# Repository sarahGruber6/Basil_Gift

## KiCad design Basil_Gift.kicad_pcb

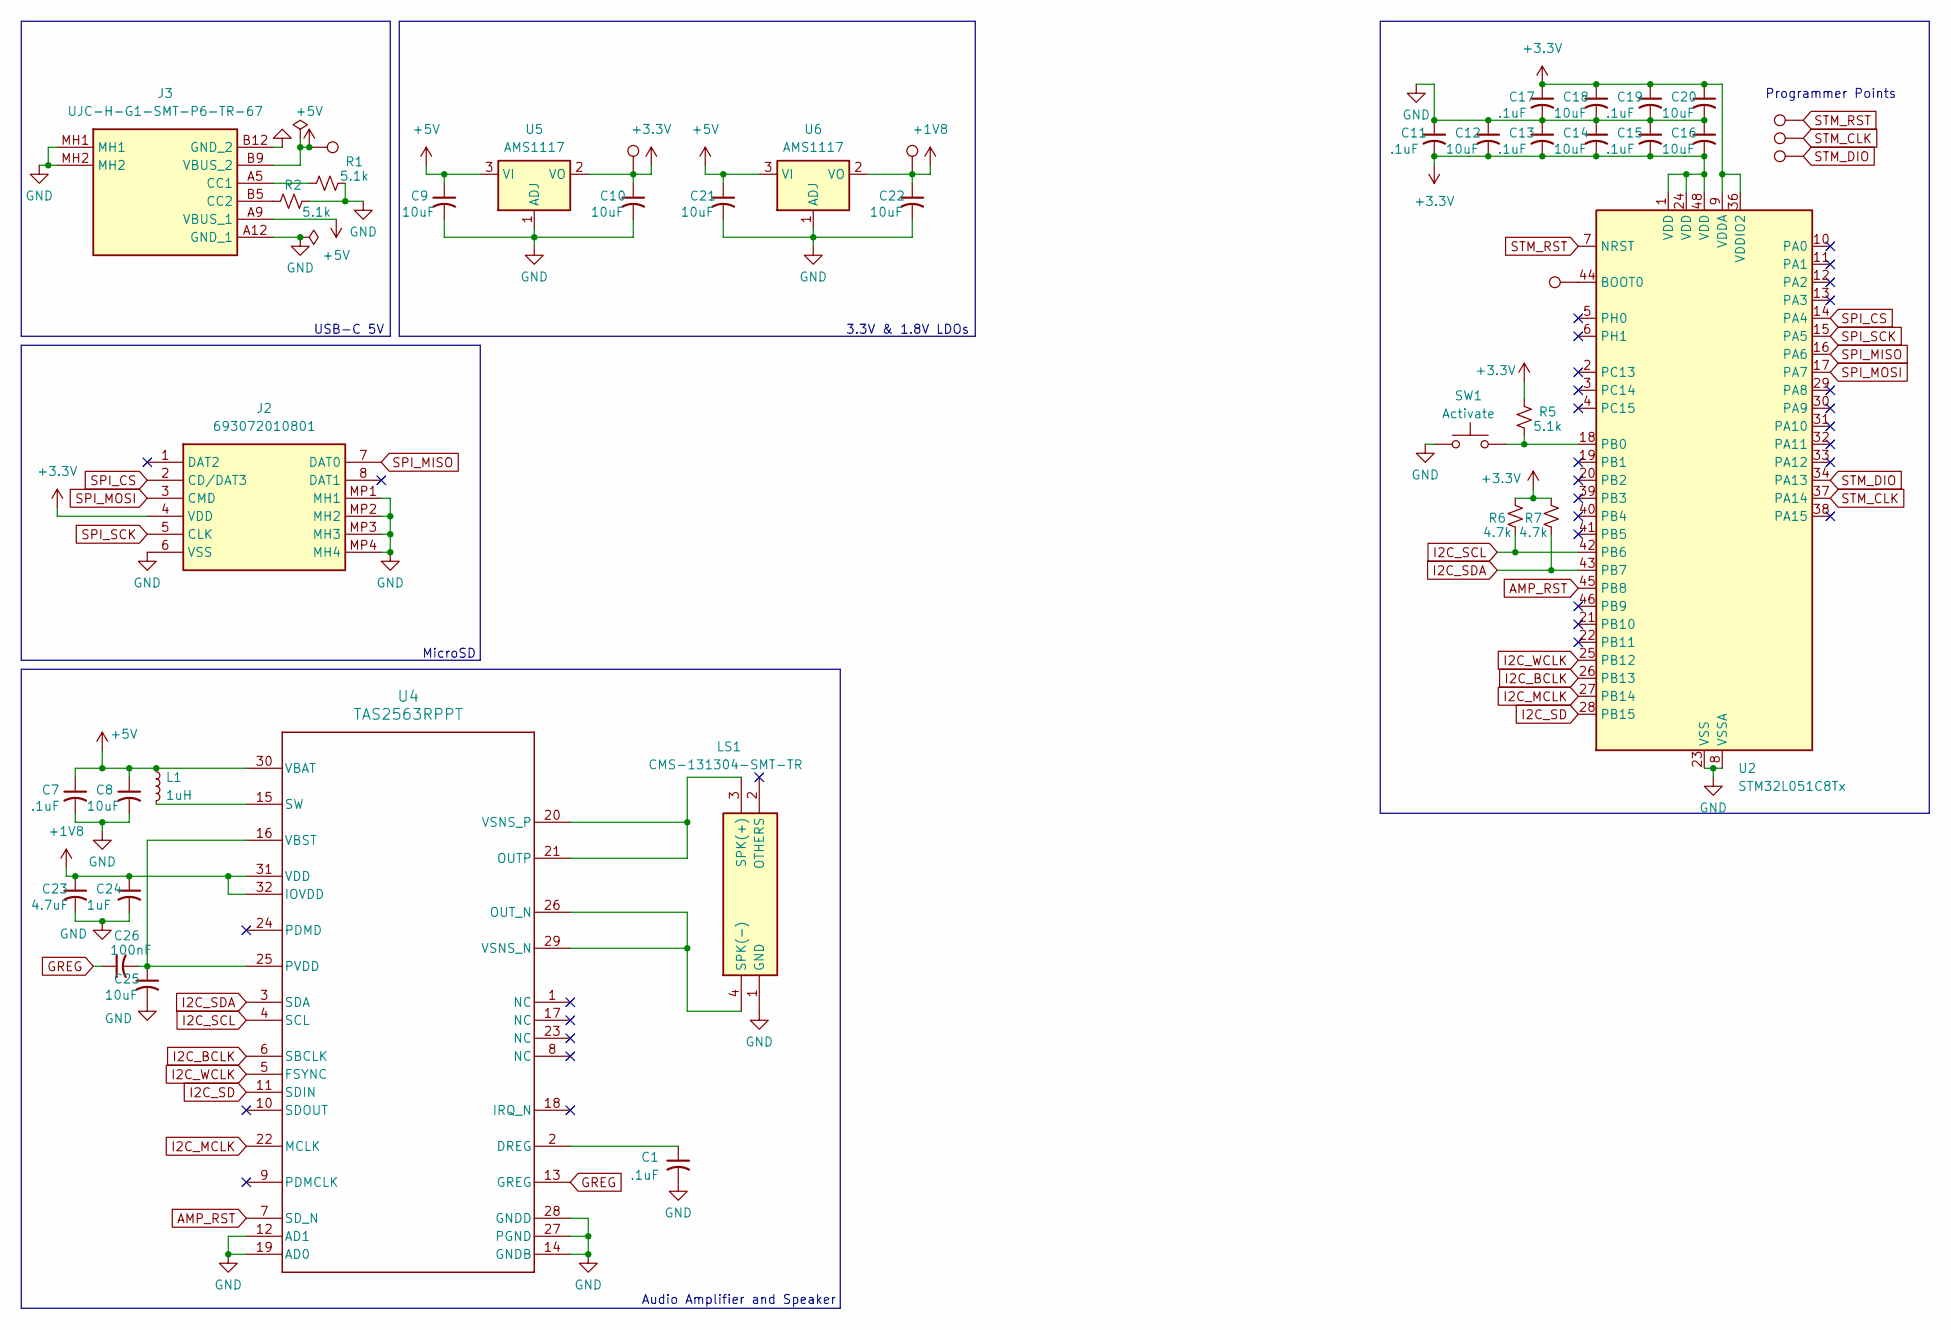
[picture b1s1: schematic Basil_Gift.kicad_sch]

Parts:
C1, C7, C11, C13, C15, C17, C19: .1uF; C_0603_1608Metric_Pad1.08x0.95mm_HandSolder
C8, C9, C10, C12, C14, C16, C18, C20, C21, C22, C25: 10uF; C_0603_1608Metric_Pad1.08x0.95mm_HandSolder
C23: 4.7uF; C_0603_1608Metric_Pad1.08x0.95mm_HandSolder
C24: 1uF; C_0603_1608Metric_Pad1.08x0.95mm_HandSolder
C26: 100nF; C_0603_1608Metric_Pad1.08x0.95mm_HandSolder
J2: 693072010801; Mouser Part Number 710-693072010801
J3: UJC-H-G1-SMT-P6-TR-67; UJCHG1SMTP6TR67; Manufacturer_Part_Number UJC-H-G1-SMT-P6-TR-67
L1: 1uH; L_0603_1608Metric_Pad1.05x0.95mm_HandSolder
LS1: CMS-131304-SMT-TR; CMS131304SMTTR; PARTREV 1.02; Mouser Part Number 179-CMS-131304-SMTTR
R1, R2, R5: 5.1k; R_0603_1608Metric_Pad0.98x0.95mm_HandSolder
R6, R7: 4.7k; R_0603_1608Metric_Pad0.98x0.95mm_HandSolder
SW1: Activate; SW_SPST_EVQP0
TP1, TP2, TP4, TP7, TP8, TP9, TP10: TestPoint; TestPoint_Pad_D1.5mm
U2: STM32L051C8Tx; LQFP-48_7x7mm_P0.5mm
U4: TAS2563RPPT; RPP0032B-MFG
U5, U6: AMS1117; SOT-223-3_TabPin2

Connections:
+1V8: C22.1, C23.1, C24.1, TP10.1 (1_1), U4.31 (VDD), U4.32 (IOVDD), U6.2 (VO)
+3.3V: C10.1, C11.2, C12.2, C13.2, C14.2, C15.2, C16.2, C17.1, C18.1, C19.1, C20.1, J2.4 (VDD), R5.2, R6.2, R7.2, TP4.1 (1_1), U2.1 (VDD), U2.9 (VDDA), U2.24 (VDD), U2.36 (VDDIO2), U2.48 (VDD), U5.2 (VO)
+5V: C7.1, C8.1, C9.1, C21.1, J3.A9 (VBUS_1), J3.B9 (VBUS_2), L1.1, TP2.1 (1_1), U4.30 (VBAT), U5.3 (VI), U6.3 (VI)
AMP_RST: U2.45 (PB8), U4.7 (SD_N)
GND: C1.2, C7.2, C8.2, C9.2, C10.2, C11.1, C12.1, C13.1, C14.1, C15.1, C16.1, C17.2, C18.2, C19.2, C20.2, C21.2, C22.2, C23.2, C24.2, C25.2, J2.6 (VSS), J2.MP1 (MH1), J2.MP2 (MH2), J2.MP3 (MH3), J2.MP4 (MH4), J3.A12 (GND_1), J3.B12 (GND_2), J3.MH1, J3.MH2, LS1.1 (GND), R1.2, R2.2, SW1.1, U2.8 (VSSA), U2.23 (VSS), U2.35 (VSS), U2.47 (VSS), U4.12 (AD1), U4.14 (GNDB), U4.19 (AD0), U4.27 (PGND), U4.28 (GNDD), U5.1 (ADJ), U6.1 (ADJ)
GREG: C26.1, U4.13 (GREG)
I2C_BCLK: U2.26 (PB13), U4.6 (SBCLK)
I2C_MCLK: U2.27 (PB14), U4.22 (MCLK)
I2C_SCL: R6.1, U2.42 (PB6), U4.4 (SCL)
I2C_SD: U2.28 (PB15), U4.11 (SDIN)
I2C_SDA: R7.1, U2.43 (PB7), U4.3 (SDA)
I2C_WCLK: U2.25 (PB12), U4.5 (FSYNC)
unnamed: J3.A5 (CC1), R1.1
unnamed: J3.B5 (CC2), R2.1
unnamed: LS1.3 (SPK(+)), U4.20 (VSNS_P), U4.21 (OUTP)
unnamed: LS1.4 (SPK(-)), U4.26 (OUT_N), U4.29 (VSNS_N)
unnamed: TP1.1 (1_1), U2.44 (BOOT0)
unnamed: R5.1, SW1.2, U2.18 (PB0)
unnamed: C1.1, U4.2 (DREG)
unnamed: C25.1, C26.2, U4.16 (VBST), U4.25 (PVDD)
unnamed: L1.2, U4.15 (SW)
SPI_CS: J2.2 (CD/DAT3), U2.14 (PA4)
SPI_MISO: J2.7 (DAT0), U2.16 (PA6)
SPI_MOSI: J2.3 (CMD), U2.17 (PA7)
SPI_SCK: J2.5 (CLK), U2.15 (PA5)
STM_CLK: TP8.1 (1_1), U2.37 (PA14)
STM_DIO: TP9.1 (1_1), U2.34 (PA13)
STM_RST: TP7.1 (1_1), U2.7 (NRST)

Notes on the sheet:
3.3V & 1.8V LDOs
Programmer Points
MicroSD
Audio Amplifier and Speaker
USB-C 5V

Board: 2 copper layers, 42 parts (0 on the bottom side), 28 nets, no tracks yet.
